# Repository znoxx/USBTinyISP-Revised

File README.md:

# USBTinyISP programmer revised

## General

This project is derived from http://www.simpleavr.com/avr/vusbtiny

It's a cheap and easy to make ISP programmer of AVR devices.

## Contents

* eagle - contains board and schematics in Eagle CAD layout
* firmware - program itself

## What's changed

* Issues in schematics corrected
* Aligned with newer V-USB stack
* Board layout optimized for "toner transfer" method and one layer
* SMD 0805 design

## How to build

To compile, you will need AVR-GCC stack. Just run **make** in firmware directory or flash pre-build vusbtiny.hex into the freshly build board.

### Fuse bit settings

* lfuse: 0xe1
* hfuse: 0x5d
* efuse: 0xff

## Further reading

Please refer to http://znoxx.me/2013/03/10/usbtinyisp_ili_opyat__programmator/ for description and some pictures. (In Russian, use "Translate"
 button in menu to translate to your language)

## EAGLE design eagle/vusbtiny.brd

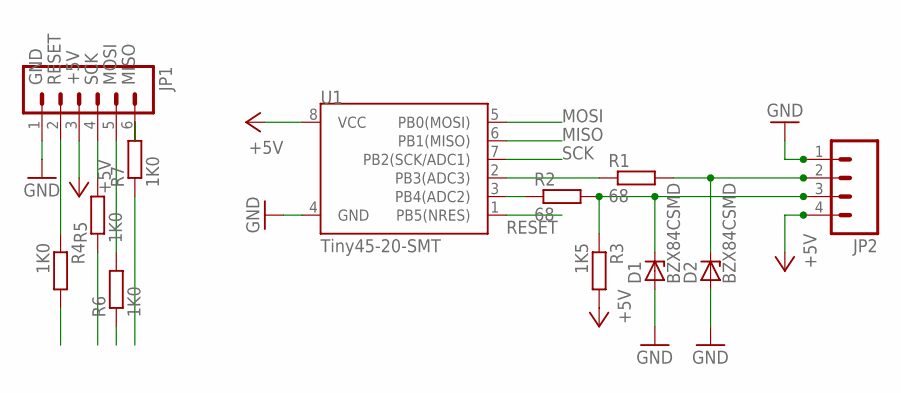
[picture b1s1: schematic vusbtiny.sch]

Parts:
D1, D2: BZX84CSMD; TO236
JP1: M06LONGPADS; 1X06_LONGPADS
JP2: M04LONGPADS; 1X04_LONGPADS
R1, R2: 68; R0805
R3: 1K5; R0805
R4, R5, R6, R7: 1K0; R0805
U1: Tiny45-20-SMT; SO08-EIAJ

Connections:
+5V: JP1.3, JP2.4, R3.2, U1.8 (VCC)
GND: D1.A, D2.A, JP1.1, JP2.1, U1.4 (GND)
MISO: R7.1, U1.6 (PB1(MISO))
MOSI: R6.1, U1.5 (PB0(MOSI))
unnamed: R1.1, U1.2 (PB3(ADC3))
unnamed: R2.1, U1.3 (PB4(ADC2))
unnamed: D2.C, JP2.2, R1.2
unnamed: JP1.2, R4.1
unnamed: JP1.4, R5.2
unnamed: JP1.5, R6.2
unnamed: JP1.6, R7.2
unnamed: D1.C, JP2.3, R2.2, R3.1
RESET: R4.2, U1.1 (PB5(NRES))
SCK: R5.1, U1.7 (PB2(SCK/ADC1))

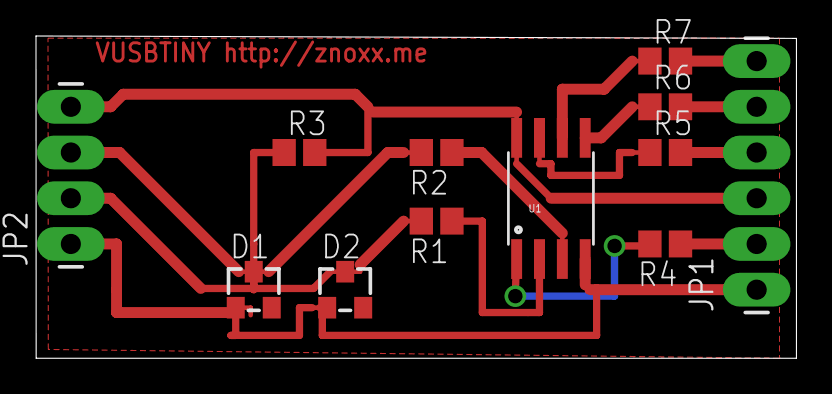
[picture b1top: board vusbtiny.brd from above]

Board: 2 copper layers, 42.2 x 17.9 mm, 12 parts (0 on the bottom side), 14 nets.

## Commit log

2016-04-26 :boom::camel: Added .gitattributes & .gitignore files
2016-04-26 Initial commit to github
    Published on GITHUB

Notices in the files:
parts and their libraries:
SparkFun-DigitalIC: Licensing: CC v3.0 Share-Alike You are welcome to use this library for commercial purposes.
